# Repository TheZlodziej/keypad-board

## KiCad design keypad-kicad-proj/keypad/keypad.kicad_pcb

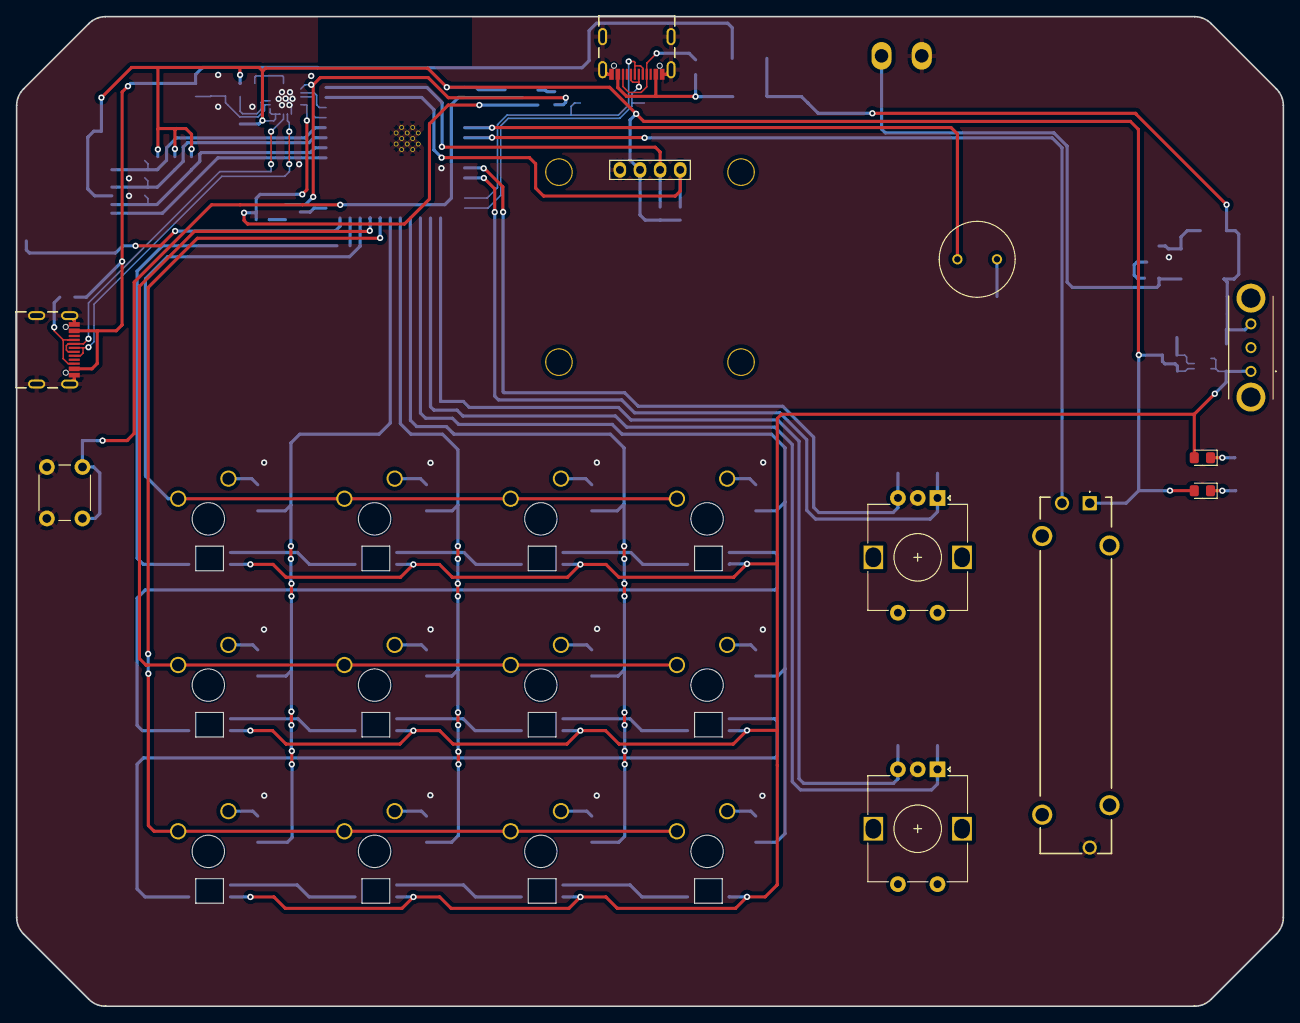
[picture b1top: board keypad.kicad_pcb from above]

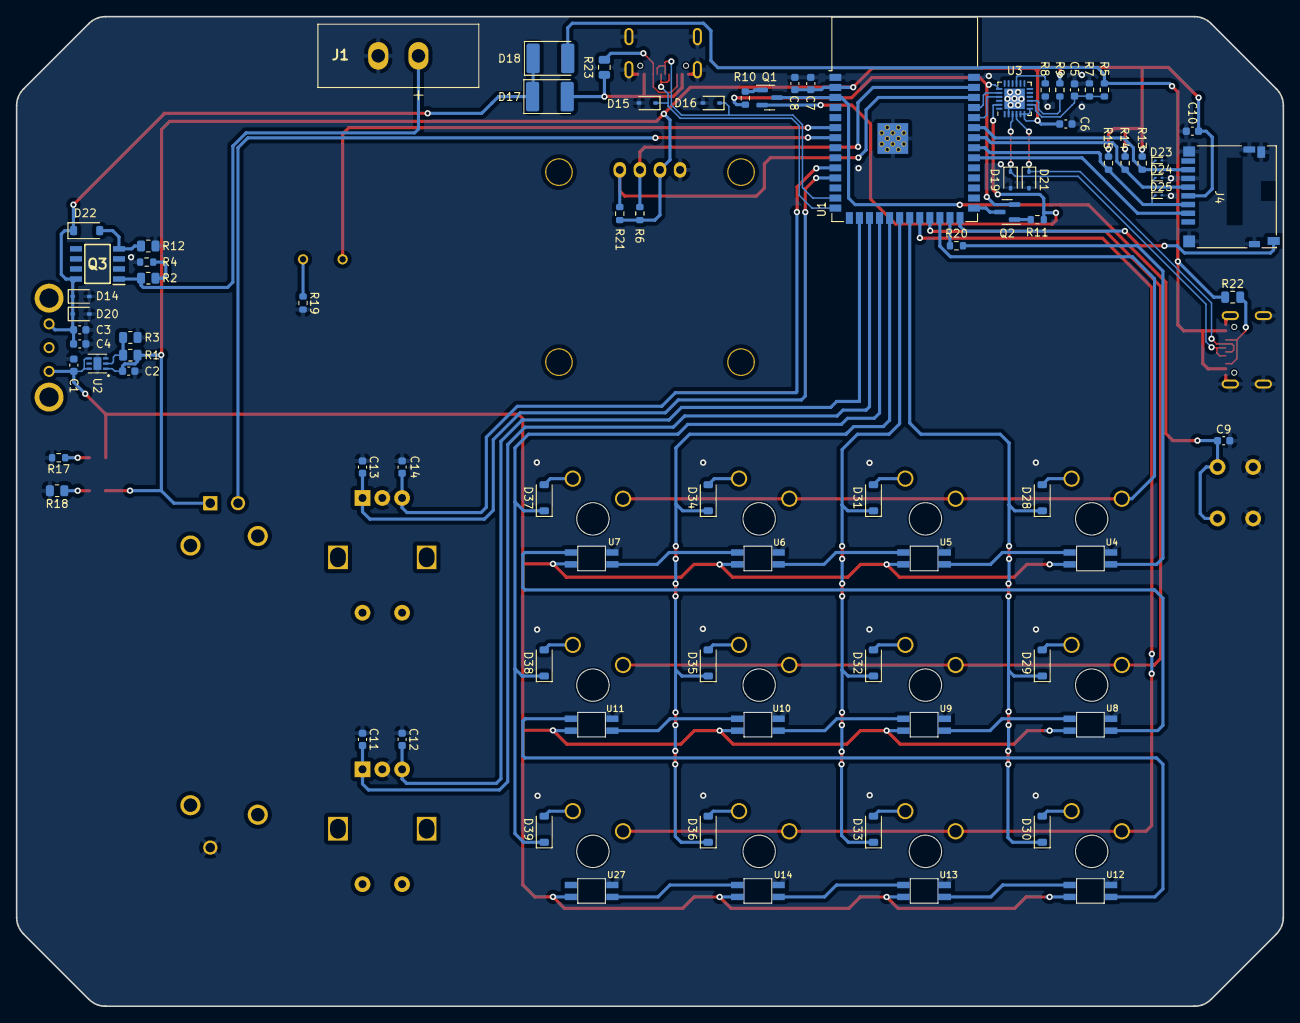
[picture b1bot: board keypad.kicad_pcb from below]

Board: 2 copper layers, 160.0 x 125.0 mm, 103 parts (80 on the bottom side), 75 nets.

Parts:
B1: Passive buzzer; CMI9605IC0580T
Brd1: SSD1306; 128x64OLED_V2
C1, C2, C5, C9, C11, C12, C13, C14: 1uF; C_0603_1608Metric
C3, C4, C6, C7, C10: 10uF; C_0603_1608Metric
C8: 0.1uF; C_0603_1608Metric
D14, D15, D16, D19, D20, D21: SD15_SOD323; D_SOD-323
D17, D18: D_Schottky; D_2114_3652Metric
D22, D28, D29, D30, D31, D32, D33, D34, D35, D36, D37, D38, D39: D_Small; D_SOD-123
D23, D24, D25: ESD9B3.3ST5G; D_SOD-923
D26, D27: LED; LED_0805_2012Metric_Pad1.15x1.40mm_HandSolder
J1: Screw_Terminal_01x02; XY2500R-DS(5.08)-02V
J2, J3: USB4105-GF-A; GCT_USB4105-GF-A
J4: Micro_SD_Card_Det_Hirose_DM3AT; microSD_HC_Hirose_DM3D-SF
Q1, Q2: BC817; SOT-23
Q3: IRF9393TRPBF; SOIC127P600X175-8N
R1, R12: 100k; R_0805_2012Metric
R2: 1M; R_0805_2012Metric
R3: 20k; R_0805_2012Metric
R4: 249k; R_0603_1608Metric
R5: 22.1k; R_0603_1608Metric
R6, R21: 4k7; R_0603_1608Metric
R7: 47.5k; R_0603_1608Metric
R8, R10, R11, R13, R14, R15: 10k; R_0603_1608Metric
R9, R17: 1k; R_0603_1608Metric
R18: 680; R_0805_2012Metric
R19: 200; R_0603_1608Metric
R20: 220; R_0603_1608Metric
R22, R23: 56k; C_0805_2012Metric
RV1: R_Potentiometer_Small; PTA30432010CIB102
S1: WS-SLSU_Slide_Switch; EG1206A
SW1, SW2: RotaryEncoder; RotaryEncoder_Alps_EC12E-Switch_Vertical_H20mm
SW25: SW_RST; SW_PUSH_6mm
SW26, SW27, SW28, SW32, SW33, SW34, SW38, SW39, SW40, SW44, SW45, SW46: Cherry_MX; MX1A-E1NW cherry mx blue rgb
U1: ESP32-S3-WROOM-1
U2: TLV75901PDRVT
U3: CP2102N-A01-GQFN24; QFN-24-1EP_4x4mm_P0.5mm_EP2.6x2.6mm
U4, U5, U6, U7, U8, U9, U10, U11, U12, U13, U14, U27: SK6812MINI-E

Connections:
+3V3: Brd1.2 (VCC), C2.1, C6.1, C7.1, C8.1, C10.1, D27.2 (A), J4.4 (VDD), R1.1, R6.1, R9.2, R13.1, R14.1, R15.1, R21.1, RV1.1, U1.2 (3V3), U2.1 (OUT), U3.5 (VIO), U3.6 (VDD), U3.7 (REGIN)
+5V: C1.1, D26.2 (A), S1.1, U2.4 (EN), U2.6 (IN), U4.1 (VDD), U5.1 (VDD), U6.1 (VDD), U7.1 (VDD), U8.1 (VDD), U9.1 (VDD), U10.1 (VDD), U11.1 (VDD), U12.1 (VDD), U13.1 (VDD), U14.1 (VDD), U27.1 (VDD)
DTR: Q2.3 (C), U1.27 (IO0)
GND: Brd1.1 (GND), C1.2, C2.2, C3.2, C4.2, C5.2, C6.2, C7.2, C8.2, C9.2, C10.2, C11.1, C12.2, C13.1, C14.2, D14.2 (A2), D15.2 (A2), D16.2 (A2), D19.2 (A2), D20.2 (A2), D21.2 (A2), D23.2 (A2), D24.2 (A2), D25.2 (A2), J1.2, J2.A1_B12 (GND), J2.B1_A12 (GND), J2.S1 (SHELL_GND), J2.S2 (SHELL_GND), J2.S3 (SHELL_GND), J2.S4 (SHELL_GND), J3.A1_B12 (GND), J3.B1_A12 (GND), J3.S1 (SHELL_GND), J3.S2 (SHELL_GND), J3.S3 (SHELL_GND), J3.S4 (SHELL_GND), J4.6 (VSS), J4.9 (DET_B), J4.11 (SHIELD), R3.2, R4.2, R7.2, R8.2, R12.2, R17.2, R18.2, R19.2, RV1.3, SW1.C, SW2.C, SW25.1 (A), U1.1 (GND), U1.40 (GND), U1.41 (GND), U2.3 (GND), U2.7 (EPAD), U3.2 (GND), U3.25 (GND), U4.3 (GND), U5.3 (GND), U6.3 (GND), U7.3 (GND), U8.3 (GND), U9.3 (GND), U10.3 (GND), U11.3 (GND), U12.3 (GND), U13.3 (GND), U14.3 (GND), U27.3 (GND)
LCD_I2C_SCL: Brd1.4 (SDA), R21.2, U1.38 (IO2)
LCD_I2C_SDA: Brd1.3 (SCL), R6.2, U1.39 (IO1)
LED_strip: R20.2, U1.25 (IO48)
unnamed: B1.2 (-), R19.1
unnamed: D17.2 (A), J2.A4_B9 (VBUS), J2.B4_A9 (VBUS), R23.1
unnamed: D22.2 (A), Q3.4 (G), R12.1
unnamed: D26.1 (K), R17.1
unnamed: D27.1 (K), R18.1
unnamed: D28.2 (A), SW26.2
unnamed: D29.2 (A), SW27.2
unnamed: D30.2 (A), SW28.2
unnamed: D31.2 (A), SW32.2
unnamed: D32.2 (A), SW33.2
unnamed: D33.2 (A), SW34.2
unnamed: D34.2 (A), SW38.2
unnamed: D35.2 (A), SW39.2
unnamed: D36.2 (A), SW40.2
unnamed: D37.2 (A), SW44.2
unnamed: D38.2 (A), SW45.2
unnamed: D39.2 (A), SW46.2
unnamed: J1.1, Q3.1 (S_1), R2.1
unnamed: J2.A5 (CC1), J2.B5 (CC2), R23.2
unnamed: J3.A5 (CC1), J3.B5 (CC2), R22.2
unnamed: Q1.1 (B), R10.1
unnamed: Q1.2 (E), R11.2, U3.23 (DTR)
unnamed: Q2.1 (B), R11.1
unnamed: Q2.2 (E), R10.2, U3.19 (RTS)
unnamed: R1.2, R3.1, U2.2 (FB)
unnamed: C5.1, R5.2, R7.1, U3.8 (VBUS)
unnamed: R9.1, U3.9 (~RSTb)
unnamed: R8.1, U3.15 (~SUSPENDb)
unnamed: R20.1, U4.4 (DIN)
unnamed: U4.2 (DOUT), U5.4 (DIN)
unnamed: U5.2 (DOUT), U6.4 (DIN)
unnamed: U6.2 (DOUT), U7.4 (DIN)
unnamed: U7.2 (DOUT), U8.4 (DIN)
unnamed: U8.2 (DOUT), U9.4 (DIN)
unnamed: U9.2 (DOUT), U10.4 (DIN)
unnamed: U10.2 (DOUT), U11.4 (DIN)
unnamed: U11.2 (DOUT), U12.4 (DIN)
unnamed: U12.2 (DOUT), U13.4 (DIN)
unnamed: U13.2 (DOUT), U14.4 (DIN)
unnamed: U14.2 (DOUT), U27.4 (DIN)
RTS: C9.1, Q1.3 (C), SW25.2 (B), U1.3 (EN)
SD_CLK: D24.1 (A1), J4.5 (CLK), R14.2, U1.34 (IO41)
SD_CS: J4.2 (DAT3/CD), U1.32 (IO39)
SD_DET: J4.10 (DET_A), U1.26 (IO45)
SD_MISO: D23.1 (A1), J4.7 (DAT0), R13.2, U1.35 (IO42)
SD_MOSI: D25.1 (A1), J4.3 (CMD), R15.2, U1.33 (IO40)
UART_RX: U1.37 (TXD0), U3.20 (RXD)
UART_TX: U1.36 (RXD0), U3.21 (TXD)
USB-C_OTG_5V: C3.1, C4.1, D14.1 (A1), D17.1 (K), D18.1 (K), D20.1 (A1), D22.1 (K), Q3.8 (D_4), S1.3
USB-C_OTG_D+: D15.1 (A1), J2.A6 (DP1), J2.B6 (DP2), U1.14 (IO20)
USB-C_OTG_D-: D16.1 (A1), J2.A7 (DN1), J2.B7 (DN2), U1.13 (IO19)
USB-C_UART_D+: D19.1 (A1), J3.A6 (DP1), J3.B6 (DP2), U3.3 (D+)
USB-C_UART_D-: D21.1 (A1), J3.A7 (DN1), J3.B7 (DN2), U3.4 (D-)
USB-C_UART_VBUS: D18.2 (A), J3.A4_B9 (VBUS), J3.B4_A9 (VBUS), R5.1, R22.1
battery_test: R2.2, R4.1
buzzer: B1.1 (+), U1.6 (IO6)
col_0: D28.1 (K), D29.1 (K), D30.1 (K), U1.21 (IO13)
col_1: D31.1 (K), D32.1 (K), D33.1 (K), U1.20 (IO12)
col_2: D34.1 (K), D35.1 (K), D36.1 (K), U1.19 (IO11)
col_3: D37.1 (K), D38.1 (K), D39.1 (K), U1.18 (IO10)
rotary_encoder_1A: C11.2, SW1.A, U1.17 (IO9)
rotary_encoder_1B: C12.1, SW1.B, U1.16 (IO46)
rotary_encoder_2A: C13.2, SW2.A, U1.11 (IO18)
rotary_encoder_2B: C14.1, SW2.B, U1.10 (IO17)
row_0: SW26.1, SW32.1, SW38.1, SW44.1, U1.24 (IO47)
row_1: SW27.1, SW33.1, SW39.1, SW45.1, U1.23 (IO21)
row_2: SW28.1, SW34.1, SW40.1, SW46.1, U1.22 (IO14)
slide_potentiometer: RV1.2, U1.7 (IO7)

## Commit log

2023-11-07 init
2023-11-13 add btn matrix & led strip
2023-11-14 add usb-c interface
2023-11-14 battery source
2023-11-14 rest of the schematic
2023-11-14 keypad update
2023-11-15 footprints
2023-11-18 add all footprints & move libs to project specific
2023-11-18 move fet footprint to local lib & init pcb deisgn
2023-11-20 inital pcb layout
2023-11-20 pcb layout update
2023-11-21 full inital pcb layout
2023-11-21 update keys alignment
2023-11-21 main layout
2023-11-21 rm keypad 2ndary btns
2023-11-22 assigned different pins so it's easier for the layout
2023-11-23 layout update
2023-11-23 move libs to this repo
2023-11-23 move kicad libs to project & add relative paths
2023-11-23 update layout
2023-11-23 finish routing
2023-11-23 new cutout + 3d models
2023-11-23 micro sd slot mirror
2023-11-23 graphics
2023-11-23 papiesz
2023-11-24 small improvements & different connection in power button
2023-11-25 ldo adjustments
2023-11-25 remove encoder ref number from silkscreen
2023-11-25 prepare for production
2023-11-26 ipt file for cutout
2023-11-26 add battery charging circuit
2023-11-26 finish charging circuit, add description in front silk screen, prepare for production
2023-11-26 update routes
2023-12-01 update datasheets
2023-12-14 cleanup repo, add production files and bom
2023-12-14 add gitignore and remove DS_Store
2023-12-14 rm dsstore
2023-12-18 update project
2023-12-29 correct schematic
2024-01-02 fix board, update production files
2024-01-02 update schematic
2024-01-05 add cover file
2024-01-06 update cover project
2024-01-06 update 3d model
2024-01-06 cover adjustments
2024-01-07 add teardrops
2024-01-08 update BOM
2024-01-11 top cover v1
2024-01-20 update code according to new board
2024-01-21 fix hid
2024-01-26 test lcd

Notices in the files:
parts and their libraries:
Copyright 2016 Accelerated Designs. All rights reserved.
Copyright 2021 Accelerated Designs. All rights reserved.
